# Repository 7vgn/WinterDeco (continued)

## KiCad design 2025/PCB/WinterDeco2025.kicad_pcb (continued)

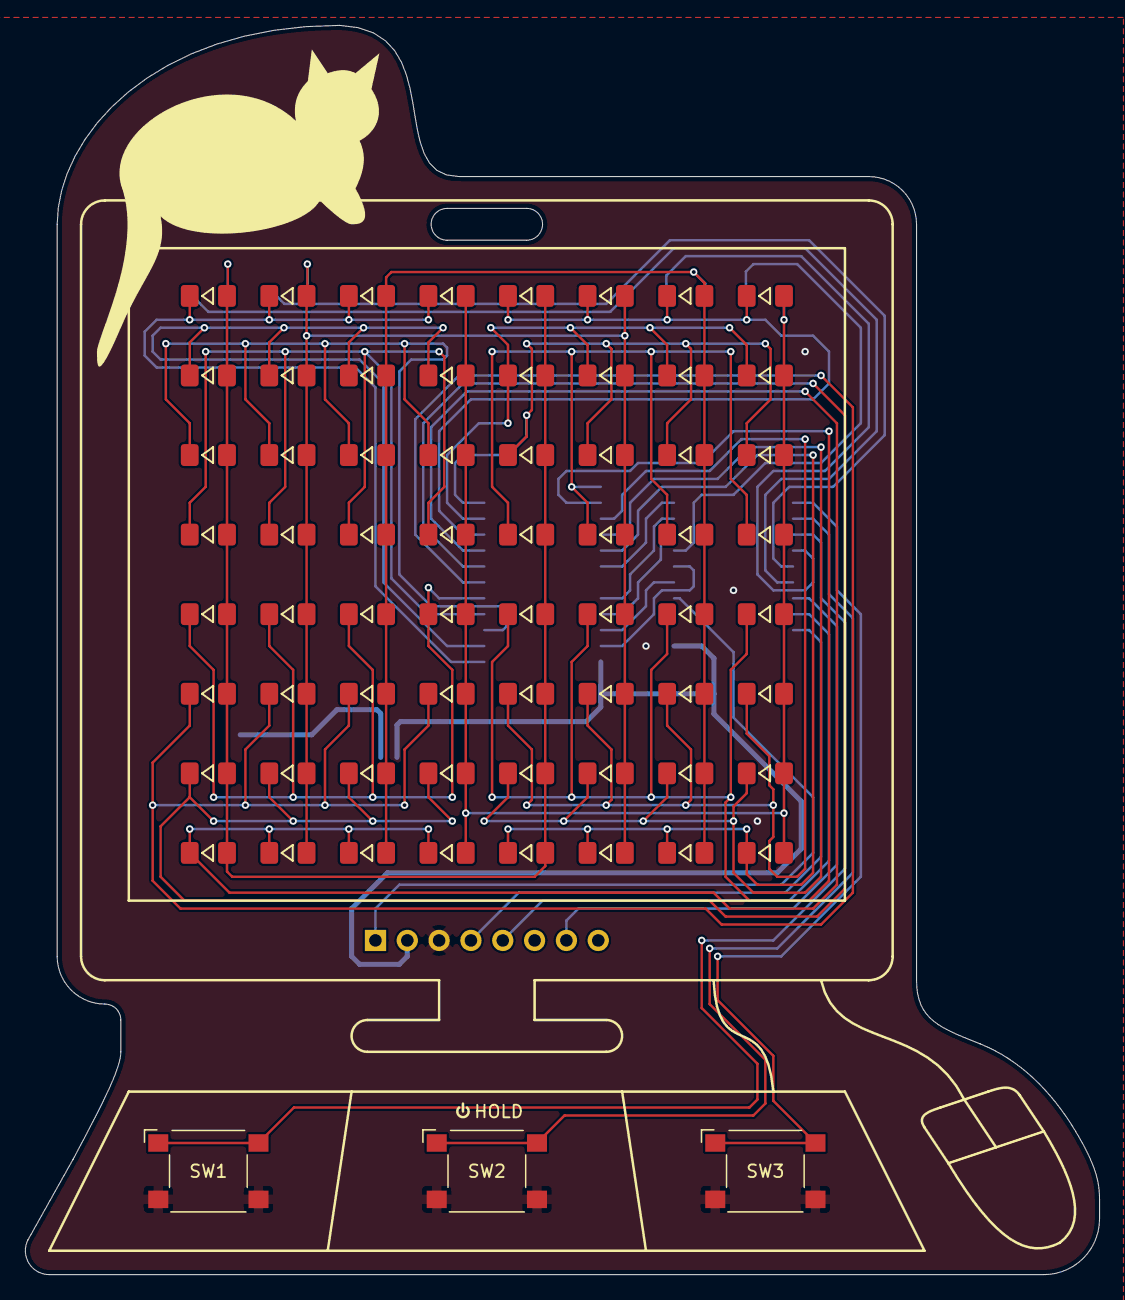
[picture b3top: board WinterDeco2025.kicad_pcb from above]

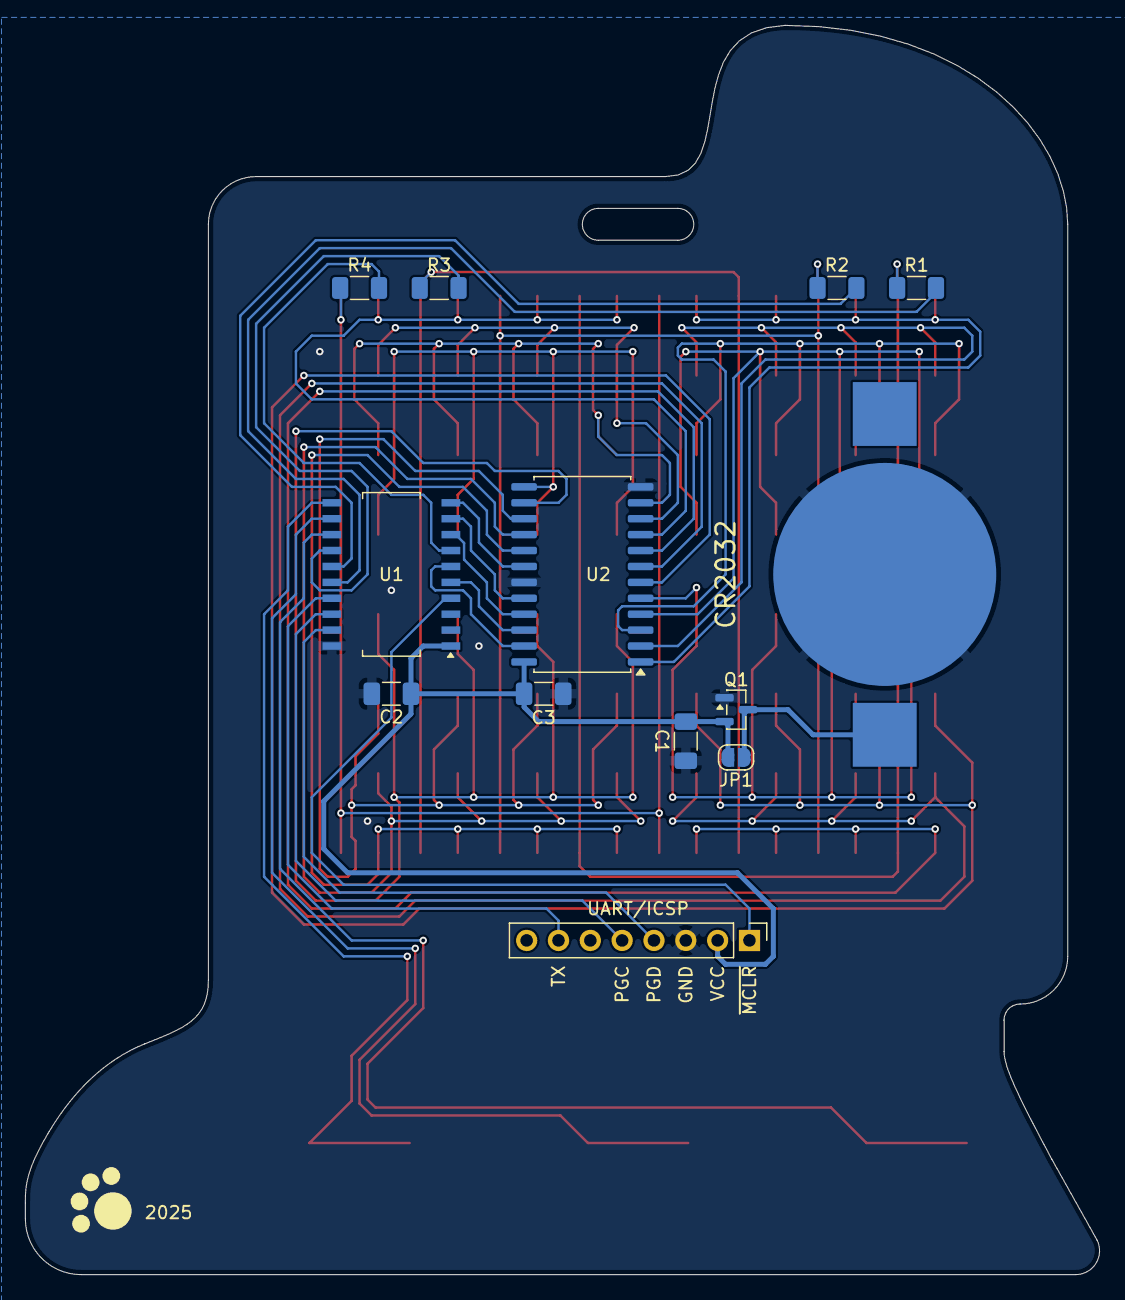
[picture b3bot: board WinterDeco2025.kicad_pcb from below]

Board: 2 copper layers, 85.7 x 99.7 mm, 80 parts (13 on the bottom side), 39 nets.

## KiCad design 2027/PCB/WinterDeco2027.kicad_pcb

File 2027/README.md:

> [!NOTE]
> This is a work in progress.

# Winter Decoration 2027

The 2027 winter-themed decoration is a spider web. This one has no buttons or touch sensors at all, using an accelerometer instead. 
As always, there is a hidden game. Can you find it without looking at the code?

## Bill of Materials

| Ref | Qty | Part | Value | Links[^links]
| --- | ---:| --- | --- | --- |
| - | 1 | PCB | 2-layer, 1.6mm thickness, purple soldermask, lead-free HASL | [J](https://jlcpcb.com/)
| BT1 | 1 | Battery Clip | CR2032, SMD mount | [M](https://mouser.com/ProductDetail/?qs=sGAEpiMZZMvxqoKe%252BDjhrhkd9JgmX6KPIe2Fc6FHFcOAlHTLYwGDJA%3D%3D) [D](https://www.digikey.com/en/products/detail/te-connectivity-linx/BAT-HLD-003-SMT-TR/14301788?s=N4IgTCBcDaIEIEEAqBaAEgGQCIoAy4GYUBlAWVSQCUQBdAXyA) [R](https://www.reichelt.de/shop/produkt/knopfzellenclip_fuer_20_mm_smd-56574)
| C1 | 1 | Capacitor | SMD 1206, 100µF, X5R | [M](https://mouser.com/ProductDetail/?qs=pUKx8fyJudDzdyEEakAKPA%3D%3D) [D](https://www.digikey.com/en/products/detail/murata-electronics/GRM31CR60J107KEA8L/16286000?s=N4IgTCBcDaIOICUCyBmAjAYQQNgAwCk1cB2AaQFEBBADgBkQBdAXyA) [R](https://www.reichelt.de/shop/produkt/mlcc_1206_100_f_6_3_v_-10_x5r-409219)
| C2..3 | 2 | Capacitor | SMD 1206, 100nF, X7R | [M](https://mouser.com/ProductDetail/?qs=Jm2GQyTW%2Fbgjukwx9JJFzw%3D%3D) [D](https://www.digikey.com/en/products/detail/kyocera-avx/KGM31DR72A104KU/563639?s=N4IgTCBcDaIIxgAwDY4GE6ICwGkCCAKmHiALoC%2BQA) [R](https://www.reichelt.de/shop/produkt/mlcc_1206_100_nf_100_v_-10_x7r-409241)
| C4 | 1 | Capacitor | SMD 1206, 1µF, tantalum | [M](https://mouser.com/ProductDetail/?qs=rZB7yXOqaoskTND3m0TpXQ%3D%3D) [D](https://www.digikey.com/en/products/detail/kemet/T491A105K016AT/818539) [R](https://www.reichelt.de/shop/produkt/smd-tantal_1_f_16v_125_c-393782)
| D1 | 1 | Photodiode | Infrared (850nm), 3mm | [M](https://mouser.com/ProductDetail/?qs=mAH9sUMRCttalcwxTBHy7g%3D%3D) [D](https://www.digikey.com/en/products/detail/inolux/INL-3ANPD80/10384782?s=N4IgTCBcDaIJIDkAyBaAzAQQQBQCIA4AGEAXQF8g) [A](https://aliexpress.com/item/1005007219440978.html)
| D* | 31 | LED | SMD 1206, yellow | [M](https://mouser.com/ProductDetail/?qs=sGAEpiMZZMv0DJfhVcWlK%252BdbpgZMtcHOeXAaxJ3bARo%3D) [D](https://www.digikey.com/en/products/detail/liteon/LTST-C150YKT/269217?s=N4IgTCBcDaIDIBUDKCC0BhAjAVgAwE0BpBEAXQF8g) [R](https://www.reichelt.de/shop/produkt/led_smd_1206_gelb_150_mcd_120_-361548)
| D* | 1 | LED | SMD 1206, red (back side) | [M](https://mouser.com/ProductDetail/?qs=sGAEpiMZZMv0DJfhVcWlK%252BdbpgZMtcHOPtGkXd2H%2F2o%3D) [D](https://www.digikey.com/en/products/detail/liteon/LTST-C150KRKT/386761?s=N4IgTCBcDaIDIBUDKCC0BhAjAVgAwGkAlfBEAXQF8g) [R](https://www.reichelt.de/de/de/shop/produkt/led_smd_1206_rot_150_mcd_120_-361547)
| Q1[^polprot] | 1 | P-MOSFET | IRLML6402, SOT-23 | [M](https://mouser.com/ProductDetail/?qs=9%252BKlkBgLFf0HuZuONx2Ewg%3D%3D) [D](https://www.digikey.com/en/products/detail/infineon-technologies/IRLML6402TRPBF/811437) [R](https://www.reichelt.de/shop/produkt/mosfet_p-ch_-20v_-3_7a_0_065r_sot-23-108743)
| R1..4 | 4 | Resistor | SMD 1206, 68Ω | [M](https://mouser.com/ProductDetail/?qs=CteSnpDdeuDJTICysoGhNw%3D%3D) [D](https://www.digikey.com/en/products/detail/yageo/RC1206JR-0768RL/729330?s=N4IgTCBcDaIEoGECMYAMA2AUnAtKg7OgBxwAyIAugL5A) [R](https://www.reichelt.de/shop/produkt/smd-widerstand_1206_68_ohm_250_mw_5_-18364)
| R5..6 | 2 | Resistor | SMD 1206, 4.7kΩ | [M](https://mouser.com/ProductDetail/?qs=CteSnpDdeuDgOu3Rsm1uRA%3D%3D) [D](https://www.digikey.com/en/products/detail/yageo/RC1206JR-074K7L/729295?s=N4IgTCBcDaIEoGECMYAMA2AUnAtKg7ACwDS%2BAMiALoC%2BQA) [R](https://www.reichelt.de/shop/produkt/smd-widerstand_1206_4_7_kohm_250_mw_5_-18330)
| U1 | 1 | Microcontroller | PIC18F14Q41-I/REB, VQFN-20 | [M](https://mouser.com/ProductDetail/?qs=W%2FMpXkg%252BdQ7pNqp6ZZCcjA%3D%3D) [D](https://www.digikey.com/en/products/detail/microchip-technology/PIC18F14Q41-I-REB/13622176?s=N4IgTCBcDaIAoEkDCBGAHAMRQFgIrZQFoEB6AJQFEAhEAXQF8g) [R](https://www.reichelt.de/shop/produkt/8-bit-picmicro_mikrocontroller_16_kb_64_mhz_vqfn-20-311094)
| U2 | 1 | Accelerometer | ADXL345, LGA-14 | [M](https://mouser.com/ProductDetail/?qs=WIvQP4zGanhoa7YOkGtvEg%3D%3D) [D](https://www.digikey.com/en/products/detail/analog-devices-inc/ADXL345BCCZ/2034829) [A](https://aliexpress.com/item/1005008097141961.html)
| - | 1 | Piece of String | |
| - | 1 | Coin Cell | CR2032 |

[^links]: Links are just examples. Other sellers are available and similar parts can be substituted.  
[^polprot]: Q1 protects against reverse polarity and is optional. If left out, the solder jumper JP1 must be bridged instead. 

Required tools and materials: soldering iron, lead-free solder, hot air station, solder paste, tweezers, flux, isopropyl alcohol for cleaning, PIC programmer

Soldering is significantly harder than last year, since the microcontroller and the accelerometer are QFN (Quad FLat No Leads) components. If you don't have or are unfamiliar with hot-air soldering equipment, you can try using a hotplate and low-temperature solder paste (Sn42Bi58) instead.

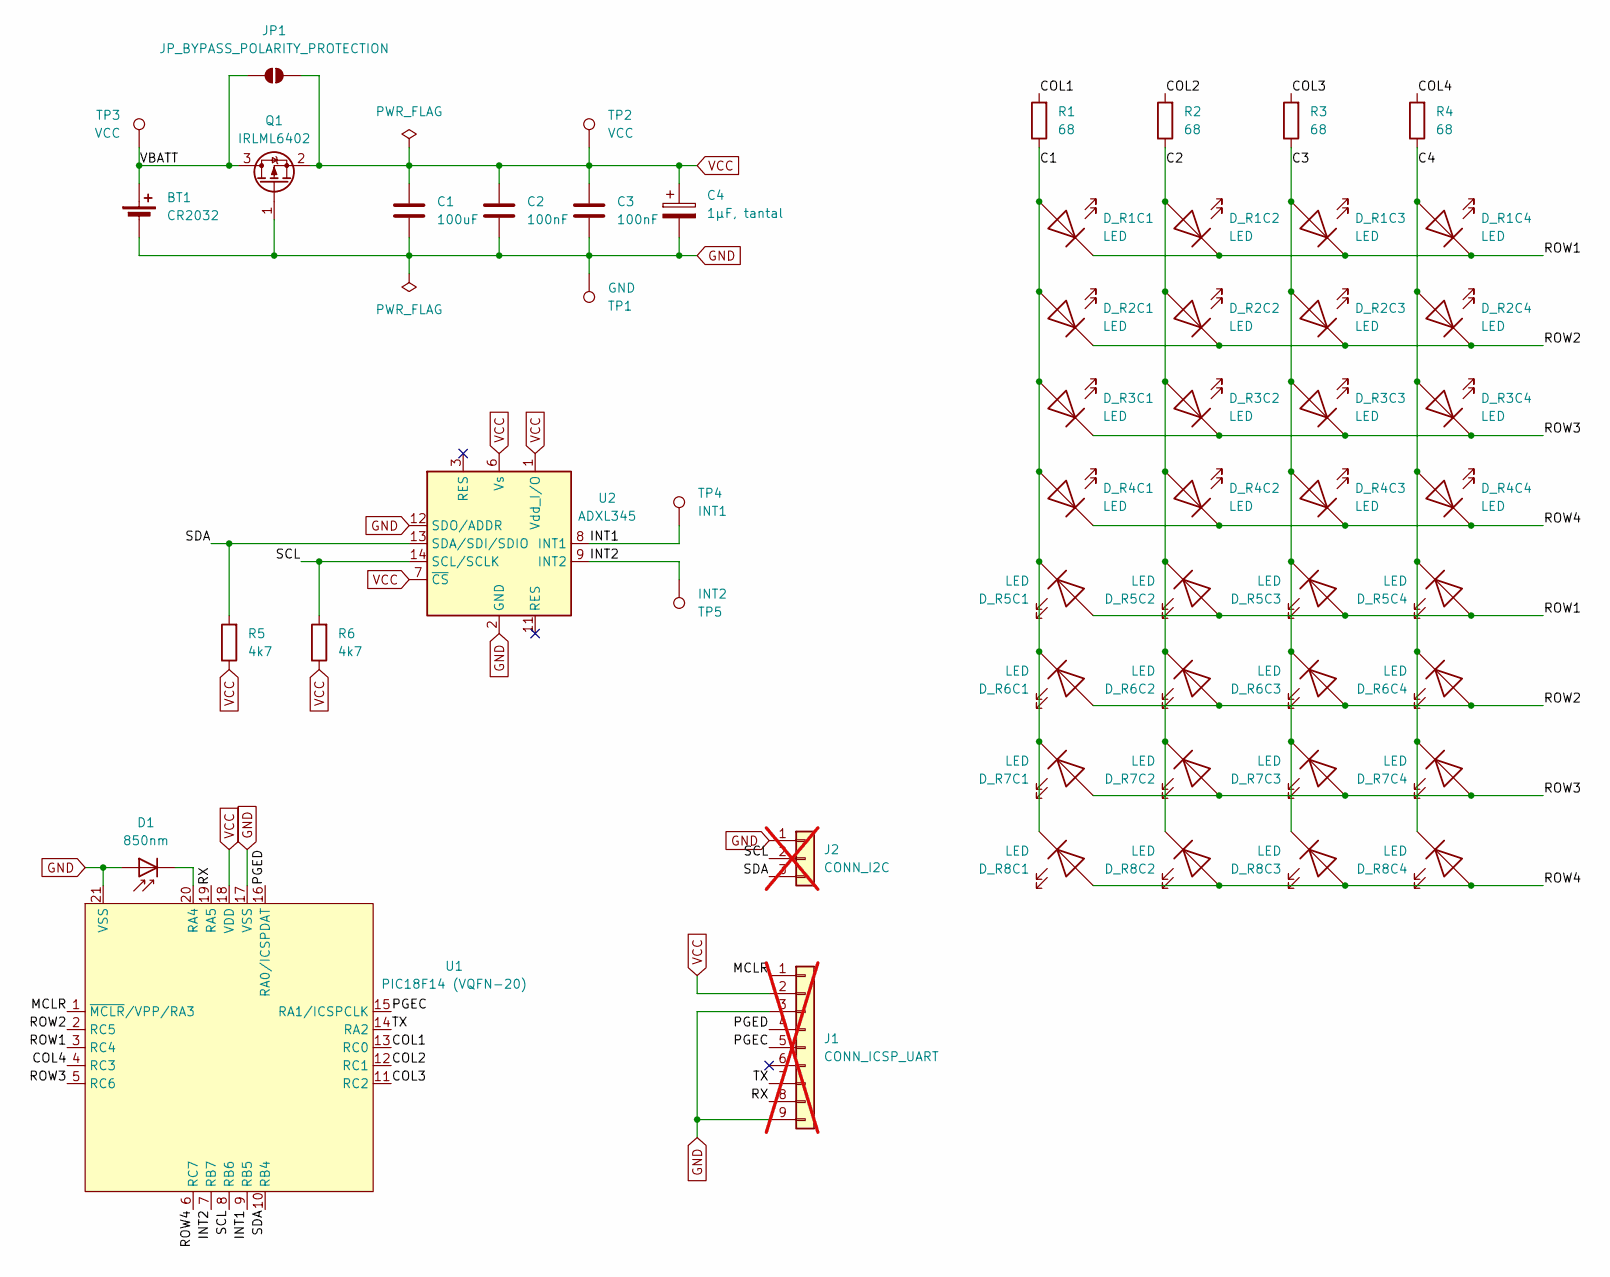
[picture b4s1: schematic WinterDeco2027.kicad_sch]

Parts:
BT1: CR2032; BatteryHolder_Keystone_3002_1x2032
C1: 100uF; C_1206_3216Metric_Pad1.33x1.80mm_HandSolder
C2, C3: 100nF; C_1206_3216Metric_Pad1.33x1.80mm_HandSolder
C4: 1µF, tantal; CP_EIA-3216-18_Kemet-A_HandSolder
D1: 850nm; LED_D3.0mm
D_R1C1, D_R1C2, D_R1C3, D_R1C4, D_R2C1, D_R2C2, D_R2C3, D_R2C4, D_R3C1, D_R3C2, D_R3C3, D_R3C4, D_R4C1, D_R4C2, D_R4C3, D_R4C4, D_R5C1, D_R5C2, D_R5C3, D_R5C4, D_R6C1, D_R6C2, D_R6C3, D_R6C4, D_R7C1, D_R7C2, D_R7C3, D_R7C4, D_R8C1, D_R8C2, D_R8C3, D_R8C4: LED; LED_1206_3216Metric_Pad1.42x1.75mm_Arrow_HandSolder
J1: CONN_ICSP_UART; PinHeader_1x09_P2.54mm_Vertical; not fitted
J2: CONN_I2C; JST_SH_BM03B-SRSS-TB_1x03-1MP_P1.00mm_Vertical; not fitted
JP1: JP_BYPASS_POLARITY_PROTECTION; SolderJumper-2_P1.3mm_Open_RoundedPad1.0x1.5mm
Q1: IRLML6402; SOT-23_Handsoldering
R1, R2, R3, R4: 68; R_1206_3216Metric_Pad1.30x1.75mm_HandSolder
R5, R6: 4k7; R_1206_3216Metric_Pad1.30x1.75mm_HandSolder
TP1: GND; TestPoint_Pad_D1.5mm
TP2, TP3: VCC; TestPoint_Pad_D1.5mm
TP4: INT1; TestPoint_Pad_D1.5mm
TP5: INT2; TestPoint_Pad_D1.5mm
U1: PIC18F14 (VQFN-20); VQFN-20-1EP_3x3mm_P0.4mm_EP1.7x1.7mm_ThermalVias
U2: ADXL345; LGA-14_3x5mm_P0.8mm_LayoutBorder1x6y

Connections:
/C1: D_R1C1.2 (A), D_R2C1.2 (A), D_R3C1.2 (A), D_R4C1.2 (A), D_R5C1.1 (K), D_R6C1.1 (K), D_R7C1.1 (K), D_R8C1.1 (K), R1.1
/C2: D_R1C2.2 (A), D_R2C2.2 (A), D_R3C2.2 (A), D_R4C2.2 (A), D_R5C2.1 (K), D_R6C2.1 (K), D_R7C2.1 (K), D_R8C2.1 (K), R2.1
/C3: D_R1C3.2 (A), D_R2C3.2 (A), D_R3C3.2 (A), D_R4C3.2 (A), D_R5C3.1 (K), D_R6C3.1 (K), D_R7C3.1 (K), D_R8C3.1 (K), R3.1
/C4: D_R1C4.2 (A), D_R2C4.2 (A), D_R3C4.2 (A), D_R4C4.2 (A), D_R5C4.1 (K), D_R6C4.1 (K), D_R7C4.1 (K), D_R8C4.1 (K), R4.1
/COL1: R1.2, U1.13 (RC0)
/COL2: R2.2, U1.12 (RC1)
/COL3: R3.2, U1.11 (RC2)
/COL4: R4.2, U1.4 (RC3)
/INT1: TP4.1 (1_1), U1.9 (RB5), U2.8 (INT1)
/INT2: TP5.1 (1_1), U1.7 (RB7), U2.9 (INT2)
/MCLR: J1.1, U1.1 (~MCLR/VPP/RA3)
/PGEC: J1.5, U1.15 (RA1/ICSPCLK)
/PGED: J1.4, U1.16 (RA0/ICSPDAT)
/ROW1: D_R1C1.1 (K), D_R1C2.1 (K), D_R1C3.1 (K), D_R1C4.1 (K), D_R5C1.2 (A), D_R5C2.2 (A), D_R5C3.2 (A), D_R5C4.2 (A), U1.3 (RC4)
/ROW2: D_R2C1.1 (K), D_R2C2.1 (K), D_R2C3.1 (K), D_R2C4.1 (K), D_R6C1.2 (A), D_R6C2.2 (A), D_R6C3.2 (A), D_R6C4.2 (A), U1.2 (RC5)
/ROW3: D_R3C1.1 (K), D_R3C2.1 (K), D_R3C3.1 (K), D_R3C4.1 (K), D_R7C1.2 (A), D_R7C2.2 (A), D_R7C3.2 (A), D_R7C4.2 (A), U1.5 (RC6)
/ROW4: D_R4C1.1 (K), D_R4C2.1 (K), D_R4C3.1 (K), D_R4C4.1 (K), D_R8C1.2 (A), D_R8C2.2 (A), D_R8C3.2 (A), D_R8C4.2 (A), U1.6 (RC7)
/RX: J1.8, U1.19 (RA5)
/SCL: J2.2, R6.2, U1.8 (RB6), U2.14 (SCL/SCLK)
/SDA: J2.3, R5.2, U1.10 (RB4), U2.13 (SDA/SDI/SDIO)
/TX: J1.7, U1.14 (RA2)
/VBATT: BT1.1 (+), JP1.1 (A), Q1.3 (D), TP3.1 (1_1)
GND: BT1.2 (-), C1.2, C2.2, C3.2, C4.2, D1.2 (A), J1.3, J1.9, J2.1, Q1.1 (G), TP1.1 (1_1), U1.17 (VSS), U1.21 (VSS), U2.2 (GND), U2.4 (GND), U2.5 (GND), U2.12 (SDO/ADDR)
unnamed: D1.1 (K), U1.20 (RA4)
VCC: C1.1, C2.1, C3.1, C4.1, J1.2, JP1.2 (B), Q1.2 (S), R5.1, R6.1, TP2.1 (1_1), U1.18 (VDD), U2.1 (Vdd_I/O), U2.6 (Vs), U2.7 (~CS)

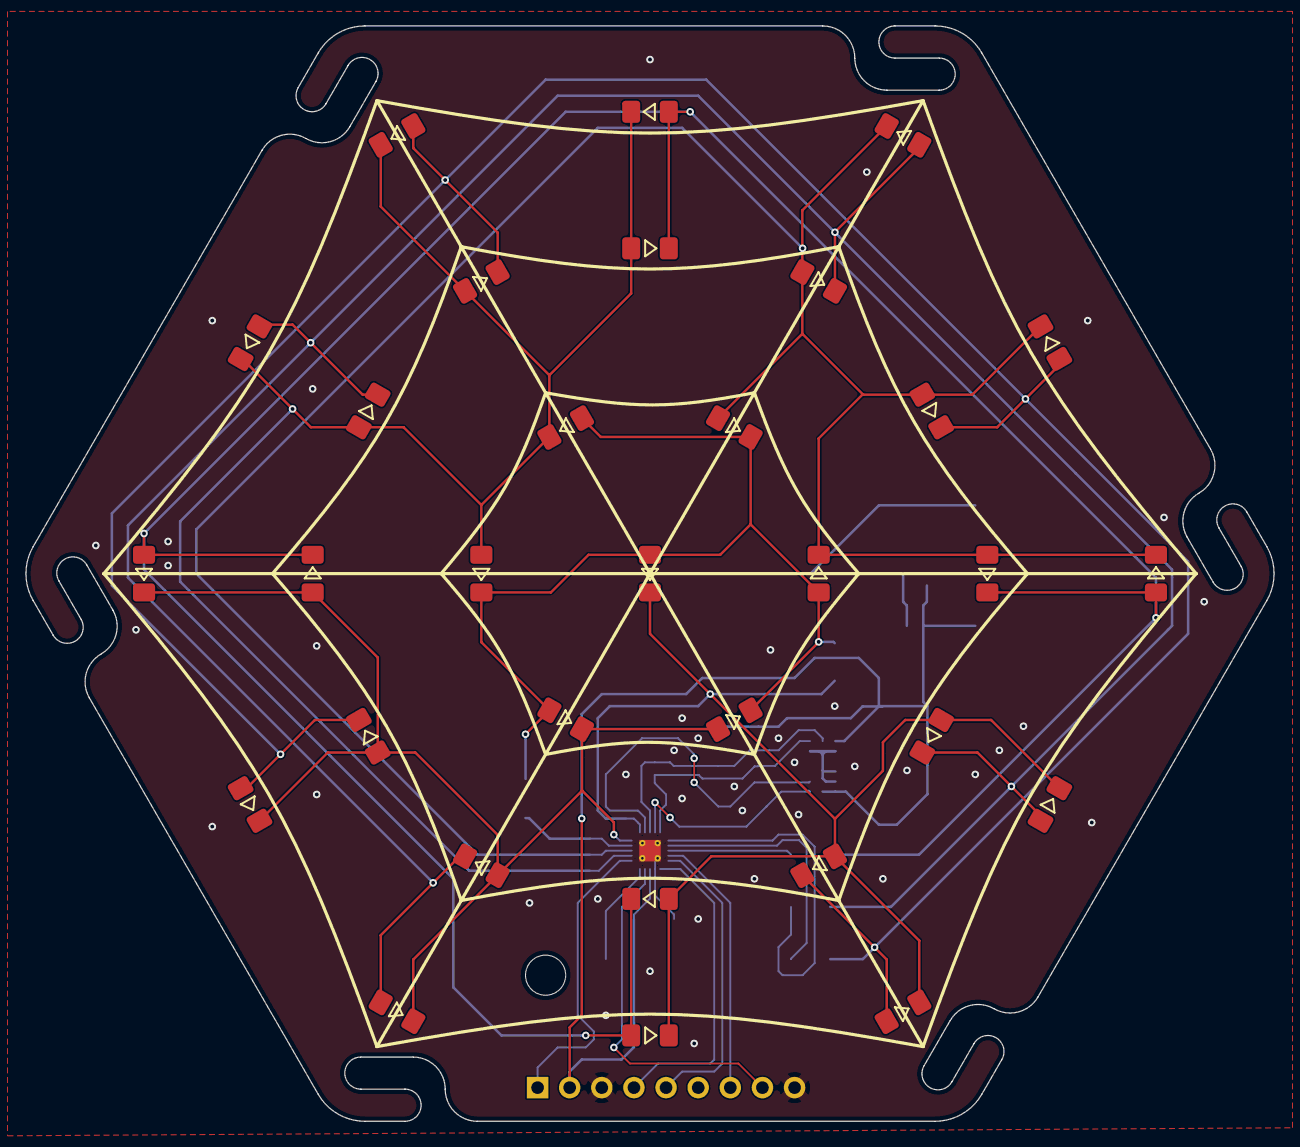
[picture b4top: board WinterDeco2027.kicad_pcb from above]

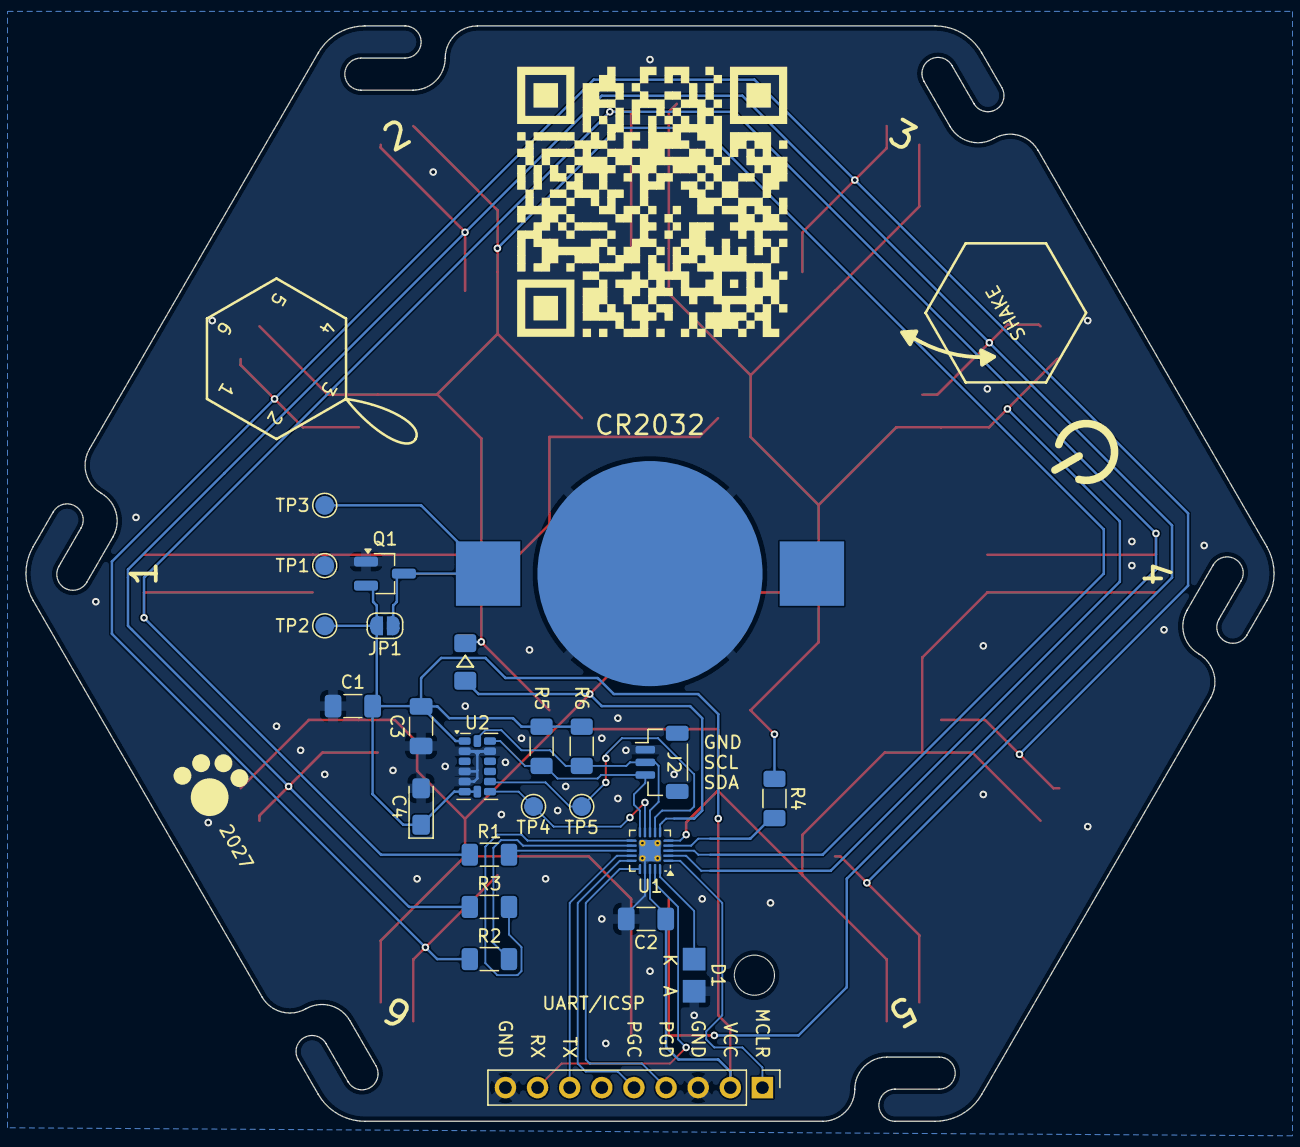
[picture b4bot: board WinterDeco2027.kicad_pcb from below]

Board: 2 copper layers, 98.7 x 86.6 mm, 55 parts (24 on the bottom side), 25 nets.

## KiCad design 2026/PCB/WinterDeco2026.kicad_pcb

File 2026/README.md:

# Winter Decoration 2026

The 2026 winter-themed decoration is a star. The touch sensors are back this year and bi-color LEDs have their debut. 
As always, there is a hidden game. Can you find it without looking at the code?

## Bill of Materials

| Ref | Qty | Part | Value | Links[^links]
| --- | ---:| --- | --- | --- |
| - | 1 | PCB | 2-layer, 1.6mm thickness, yellow soldermask, lead-free HASL | [J](https://jlcpcb.com/)
| BT1 | 1 | Battery Clip | CR2032, SMD mount | [M](https://mouser.com/ProductDetail/?qs=sGAEpiMZZMvxqoKe%252BDjhrhkd9JgmX6KPIe2Fc6FHFcOAlHTLYwGDJA%3D%3D) [D](https://www.digikey.com/en/products/detail/te-connectivity-linx/BAT-HLD-003-SMT-TR/14301788?s=N4IgTCBcDaIEIEEAqBaAEgGQCIoAy4GYUBlAWVSQCUQBdAXyA) [R](https://www.reichelt.de/shop/produkt/knopfzellenclip_fuer_20_mm_smd-56574)
| C1 | 1 | Capacitor | SMD 1206, 100µF, X5R | [M](https://mouser.com/ProductDetail/?qs=pUKx8fyJudDzdyEEakAKPA%3D%3D) [D](https://www.digikey.com/en/products/detail/murata-electronics/GRM31CR60J107KEA8L/16286000?s=N4IgTCBcDaIOICUCyBmAjAYQQNgAwCk1cB2AaQFEBBADgBkQBdAXyA) [R](https://www.reichelt.de/shop/produkt/mlcc_1206_100_f_6_3_v_-10_x5r-409219)
| C2 | 1 | Capacitor | SMD 1206, 100nF, X7R | [M](https://mouser.com/ProductDetail/?qs=Jm2GQyTW%2Fbgjukwx9JJFzw%3D%3D) [D](https://www.digikey.com/en/products/detail/kyocera-avx/KGM31DR72A104KU/563639?s=N4IgTCBcDaIIxgAwDY4GE6ICwGkCCAKmHiALoC%2BQA) [R](https://www.reichelt.de/shop/produkt/mlcc_1206_100_nf_100_v_-10_x7r-409241)
| D1..9 | 9 | LED | SMD 1210 (3227), red/green bi-color | [M](https://mouser.com/ProductDetail/?qs=%252BpvKPZD0HfH4fMARFecNqA%3D%3D) [D](https://www.digikey.com/en/products/detail/kingbright/APB3227SURKCGKC/4098592?s=N4IgTCBcDaIDYFMAmACAzGMB2EBdAvkA) [A](https://www.aliexpress.com/item/1005003327335162.html)
| D10..21 | 12 | LED | SMD 1206 (3216), yellow | [M](https://mouser.com/ProductDetail/?qs=sGAEpiMZZMv0DJfhVcWlK%252BdbpgZMtcHOeXAaxJ3bARo%3D) [D](https://www.digikey.com/en/products/detail/liteon/LTST-C150YKT/269217?s=N4IgTCBcDaIDIBUDKCC0BhAjAVgAwE0BpBEAXQF8g) [R](https://www.reichelt.de/shop/produkt/led_smd_1206_gelb_150_mcd_120_-361548)
| Q1[^polprot] | 1 | P-MOSFET | IRLML6402, SOT-23 | [M](https://mouser.com/ProductDetail/?qs=9%252BKlkBgLFf0HuZuONx2Ewg%3D%3D) [D](https://www.digikey.com/en/products/detail/infineon-technologies/IRLML6402TRPBF/811437) [R](https://www.reichelt.de/shop/produkt/mosfet_p-ch_-20v_-3_7a_0_065r_sot-23-108743)
| R1..3 | 3 | Resistor | SMD 1206, 68Ω | [M](https://mouser.com/ProductDetail/?qs=CteSnpDdeuDJTICysoGhNw%3D%3D) [D](https://www.digikey.com/en/products/detail/yageo/RC1206JR-0768RL/729330?s=N4IgTCBcDaIEoGECMYAMA2AUnAtKg7OgBxwAyIAugL5A) [R](https://www.reichelt.de/shop/produkt/smd-widerstand_1206_68_ohm_250_mw_5_-18364)
| R4 | 1 | Resistor | SMD 1206, 3.3kΩ | [M](https://mouser.com/ProductDetail/?qs=CteSnpDdeuDJAlQtfVL%252BIw%3D%3D) [D](https://www.digikey.com/en/products/detail/yageo/RC1206JR-073K3L/729267?s=N4IgTCBcDaIEoGECMYAMA2AUnAtKg7AMwDShAMiALoC%2BQA) [R](https://www.reichelt.de/shop/produkt/smd-widerstand_1206_3_3_kohm_250_mw_5_-18302)
| R5 | 1 | Resistor | SMD 1206, 4.7kΩ | [M](https://mouser.com/ProductDetail/?qs=CteSnpDdeuDgOu3Rsm1uRA%3D%3D) [D](https://www.digikey.com/en/products/detail/yageo/RC1206JR-074K7L/729295?s=N4IgTCBcDaIEoGECMYAMA2AUnAtKg7ACwDS%2BAMiALoC%2BQA) [R](https://www.reichelt.de/shop/produkt/smd-widerstand_1206_4_7_kohm_250_mw_5_-18330)
| U1 | 1 | Microcontroller | PIC18F14Q41-I/SS, TSSOP-20 | [M](https://www.mouser.com/ProductDetail/?qs=W%2FMpXkg%252BdQ7EgyN%2FoU%2FgZA%3D%3D) [D](https://www.digikey.com/en/products/detail/microchip-technology/PIC18F14Q41-I-SS/13534584?s=N4IgTCBcDaIAoEkDCBGAHAMRQFgIrZQFoEB6AZzJAF0BfIA) [R](https://www.reichelt.de/de/de/shop/produkt/8-bit-picmicro_mikrocontroller_16_kb_64_mhz_ssop-20-311093)
| - | 1 | Piece of String | |
| - | 1 | Coin Cell | CR2032 |

[^links]: Links are just examples. Other sellers are available and similar parts can be substituted.  
[^polprot]: Q1 protects against reverse polarity and is optional. If left out, the solder jumper JP1 must be bridged instead. 

Required tools and materials: soldering iron, lead-free solder, tweezers, flux, isopropyl alcohol for cleaning, PIC programmer

Soldering is slightly more challenging than in previous years, since the microcontroller is SSOP instead of SOIC.

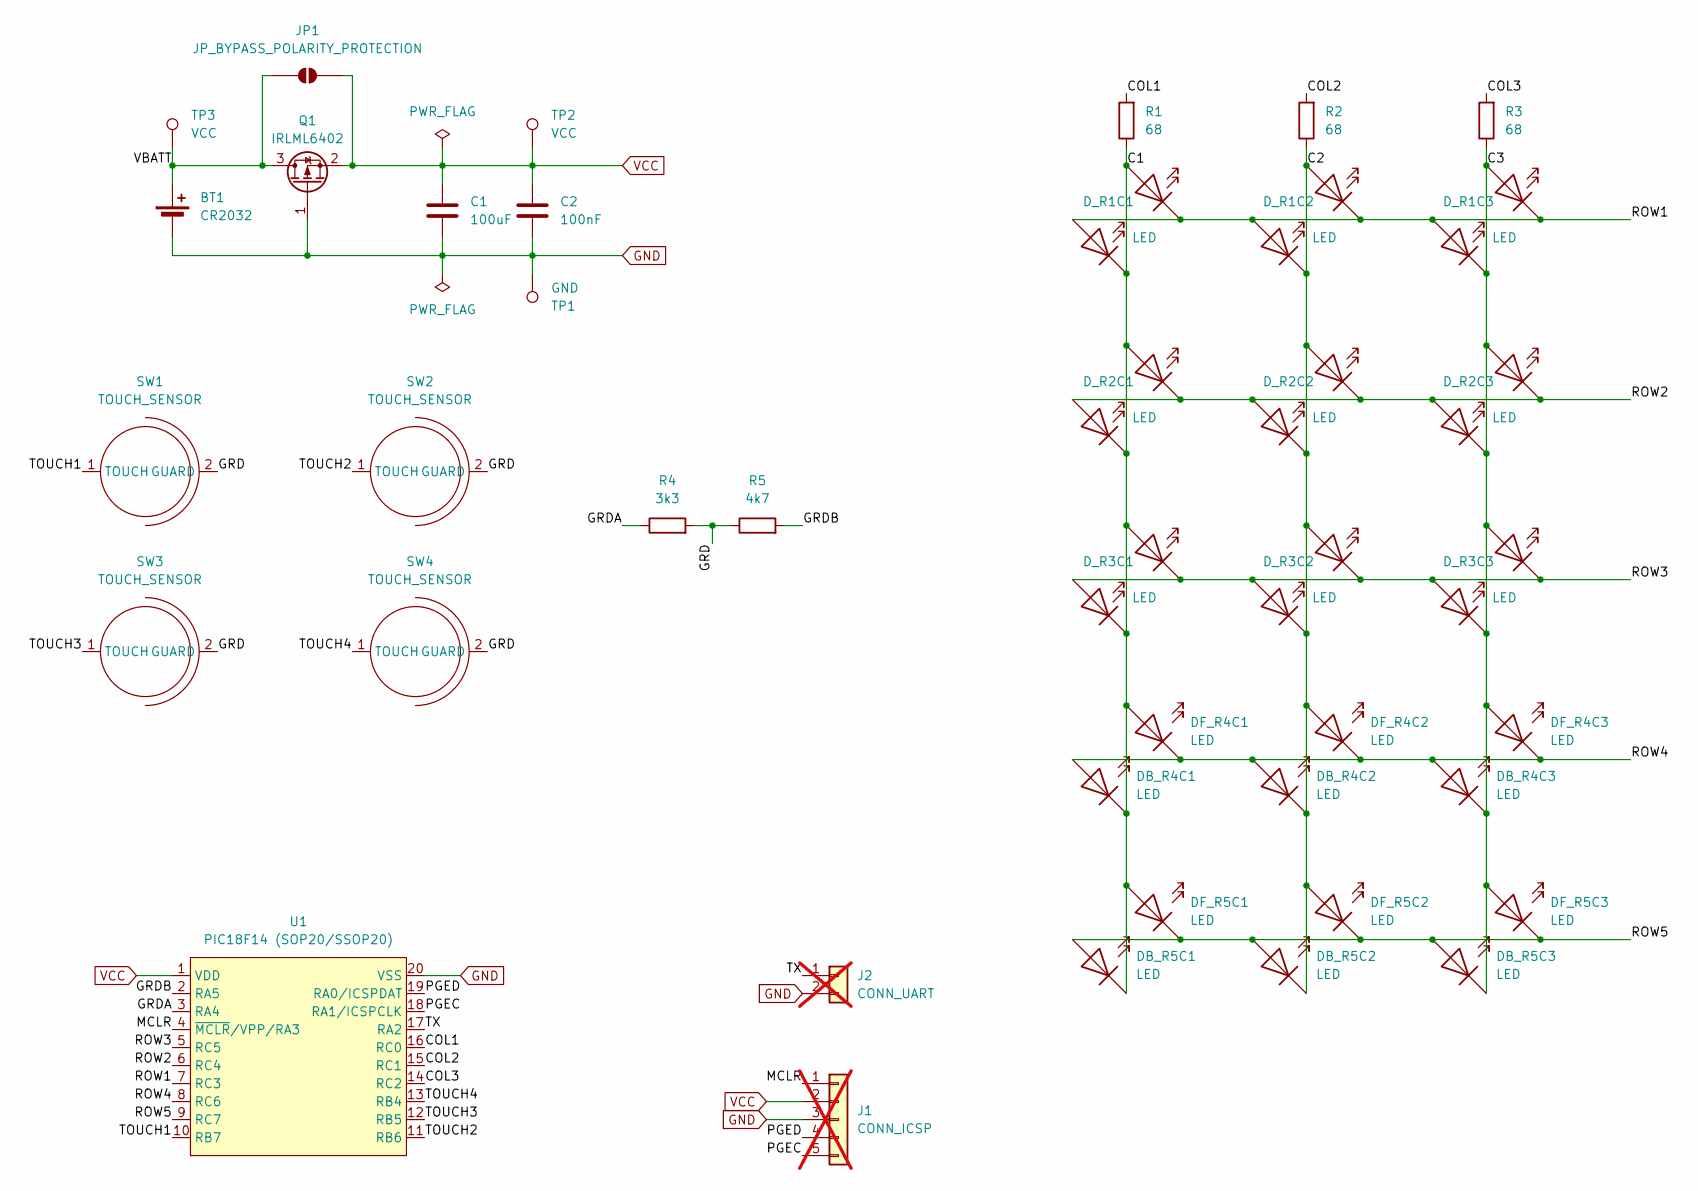
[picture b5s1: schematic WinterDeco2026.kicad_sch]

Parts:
BT1: CR2032; BatteryHolder_Keystone_3002_1x2032
C1: 100uF; C_1206_3216Metric_Pad1.33x1.80mm_HandSolder
C2: 100nF; C_1206_3216Metric_Pad1.33x1.80mm_HandSolder
DB_R4C1, DB_R4C2, DB_R4C3, DB_R5C1, DB_R5C2, DB_R5C3: LED; LED_1206_3216Metric_Pad1.42x1.75mm_Arrow_HandSolder
DF_R4C1, DF_R4C2, DF_R4C3, DF_R5C1, DF_R5C2, DF_R5C3: LED; LED_1206_3216Metric_Pad1.42x1.75mm_Arrow_HandSolder
D_R1C1, D_R1C2, D_R1C3, D_R2C1, D_R2C2, D_R2C3, D_R3C1, D_R3C2, D_R3C3: LED; LED_1210_3227_Bicolor
J1: CONN_ICSP; PinHeader_1x05_P2.54mm_Vertical; not fitted
J2: CONN_UART; PinHeader_1x02_P2.54mm_Vertical; not fitted
JP1: JP_BYPASS_POLARITY_PROTECTION; SolderJumper-2_P1.3mm_Open_RoundedPad1.0x1.5mm
Q1: IRLML6402; SOT-23_Handsoldering
R1, R2, R3: 68; R_1206_3216Metric_Pad1.30x1.75mm_HandSolder
R4: 3k3; R_1206_3216Metric_Pad1.30x1.75mm_HandSolder
R5: 4k7; R_1206_3216Metric_Pad1.30x1.75mm_HandSolder
SW1, SW2, SW3, SW4: TOUCH_SENSOR; Touch Sensor
TP1: GND; TestPoint_Pad_D1.5mm
TP2, TP3: VCC; TestPoint_Pad_D1.5mm
U1: PIC18F14 (SOP20/SSOP20); TSSOP-20_4.4x6.5mm_P0.65mm

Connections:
/C1: DB_R4C1.1 (K), DB_R5C1.1 (K), DF_R4C1.2 (A), DF_R5C1.2 (A), D_R1C1.2 (K), D_R1C1.3 (A), D_R2C1.2 (K), D_R2C1.3 (A), D_R3C1.2 (K), D_R3C1.3 (A), R1.1
/C2: DB_R4C2.1 (K), DB_R5C2.1 (K), DF_R4C2.2 (A), DF_R5C2.2 (A), D_R1C2.2 (K), D_R1C2.3 (A), D_R2C2.2 (K), D_R2C2.3 (A), D_R3C2.2 (K), D_R3C2.3 (A), R2.1
/C3: DB_R4C3.1 (K), DB_R5C3.1 (K), DF_R4C3.2 (A), DF_R5C3.2 (A), D_R1C3.2 (K), D_R1C3.3 (A), D_R2C3.2 (K), D_R2C3.3 (A), D_R3C3.2 (K), D_R3C3.3 (A), R3.1
/COL1: R1.2, U1.16 (RC0)
/COL2: R2.2, U1.15 (RC1)
/COL3: R3.2, U1.14 (RC2)
/GRD: R4.2, R5.1, SW1.2 (GUARD), SW2.2 (GUARD), SW3.2 (GUARD), SW4.2 (GUARD)
/GRDA: R4.1, U1.3 (RA4)
/GRDB: R5.2, U1.2 (RA5)
/MCLR: J1.1, U1.4 (~MCLR/VPP/RA3)
/PGEC: J1.5, U1.18 (RA1/ICSPCLK)
/PGED: J1.4, U1.19 (RA0/ICSPDAT)
/ROW1: D_R1C1.1 (A), D_R1C1.4 (K), D_R1C2.1 (A), D_R1C2.4 (K), D_R1C3.1 (A), D_R1C3.4 (K), U1.7 (RC3)
/ROW2: D_R2C1.1 (A), D_R2C1.4 (K), D_R2C2.1 (A), D_R2C2.4 (K), D_R2C3.1 (A), D_R2C3.4 (K), U1.6 (RC4)
/ROW3: D_R3C1.1 (A), D_R3C1.4 (K), D_R3C2.1 (A), D_R3C2.4 (K), D_R3C3.1 (A), D_R3C3.4 (K), U1.5 (RC5)
/ROW4: DB_R4C1.2 (A), DB_R4C2.2 (A), DB_R4C3.2 (A), DF_R4C1.1 (K), DF_R4C2.1 (K), DF_R4C3.1 (K), U1.8 (RC6)
/ROW5: DB_R5C1.2 (A), DB_R5C2.2 (A), DB_R5C3.2 (A), DF_R5C1.1 (K), DF_R5C2.1 (K), DF_R5C3.1 (K), U1.9 (RC7)
/TOUCH1: SW1.1 (TOUCH), U1.10 (RB7)
/TOUCH2: SW2.1 (TOUCH), U1.11 (RB6)
/TOUCH3: SW3.1 (TOUCH), U1.12 (RB5)
/TOUCH4: SW4.1 (TOUCH), U1.13 (RB4)
/TX: J2.1, U1.17 (RA2)
/VBATT: BT1.1 (+), JP1.1 (A), Q1.3 (D), TP3.1 (1_1)
GND: BT1.2 (-), C1.2, C2.2, J1.3, J2.2, Q1.1 (G), TP1.1 (1_1), U1.20 (VSS)
VCC: C1.1, C2.1, J1.2, JP1.2 (B), Q1.2 (S), TP2.1 (1_1), U1.1 (VDD)

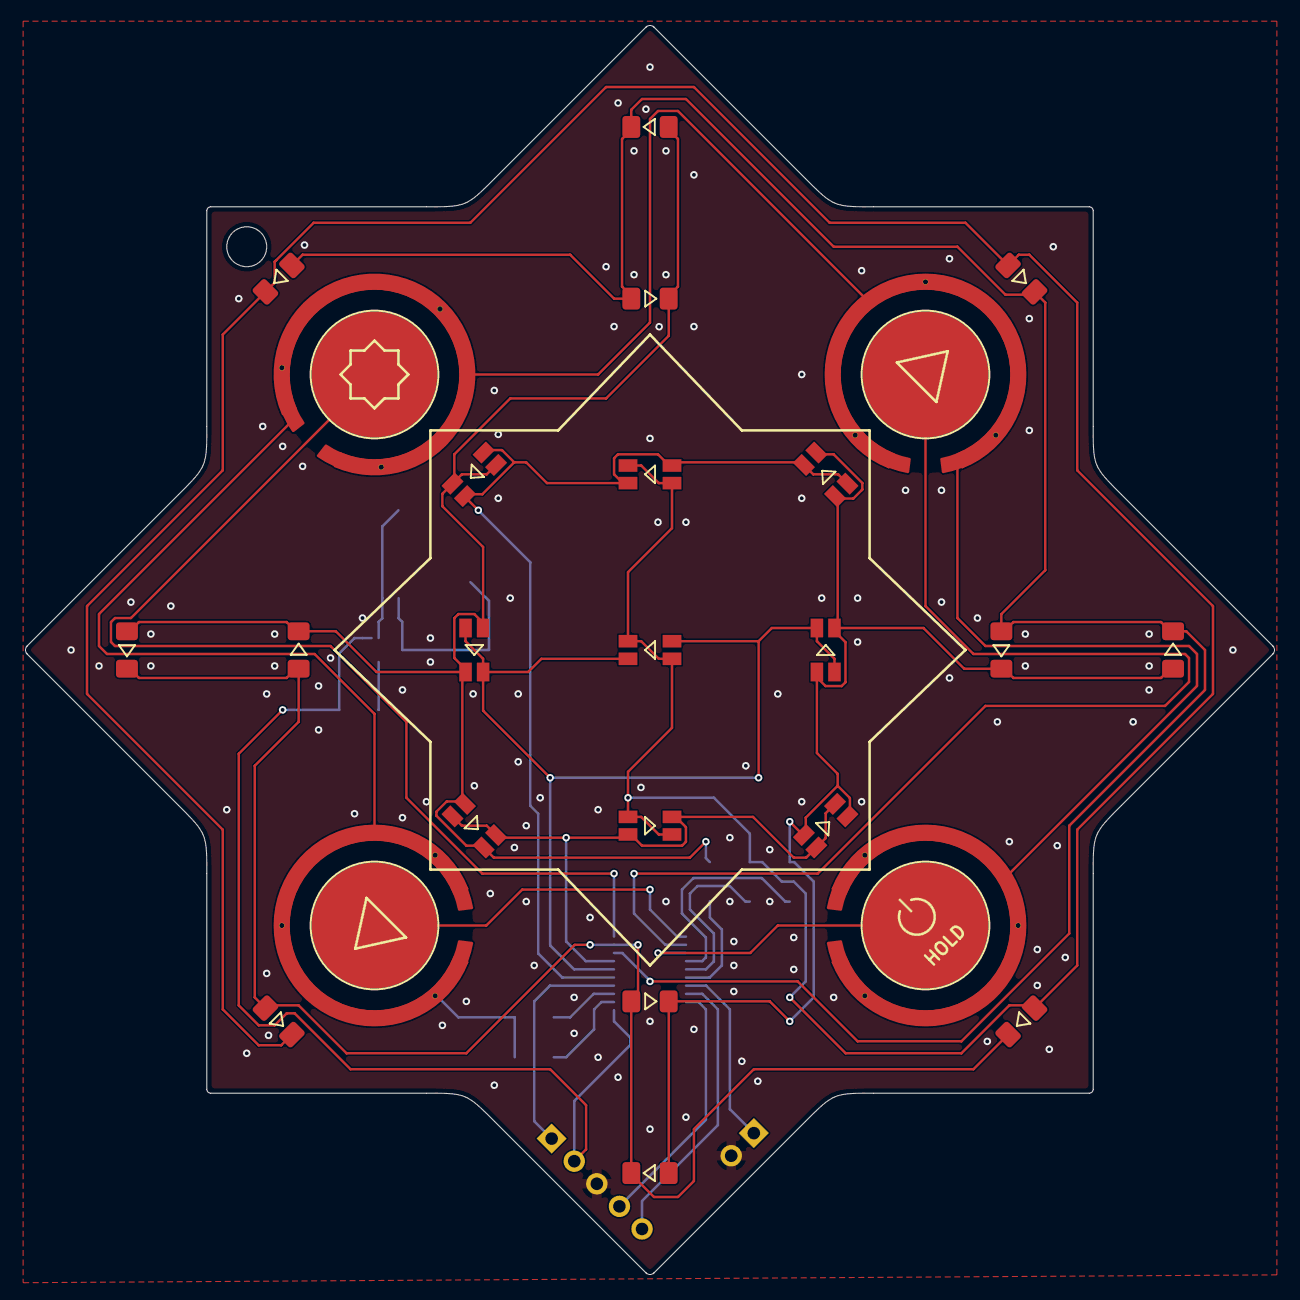
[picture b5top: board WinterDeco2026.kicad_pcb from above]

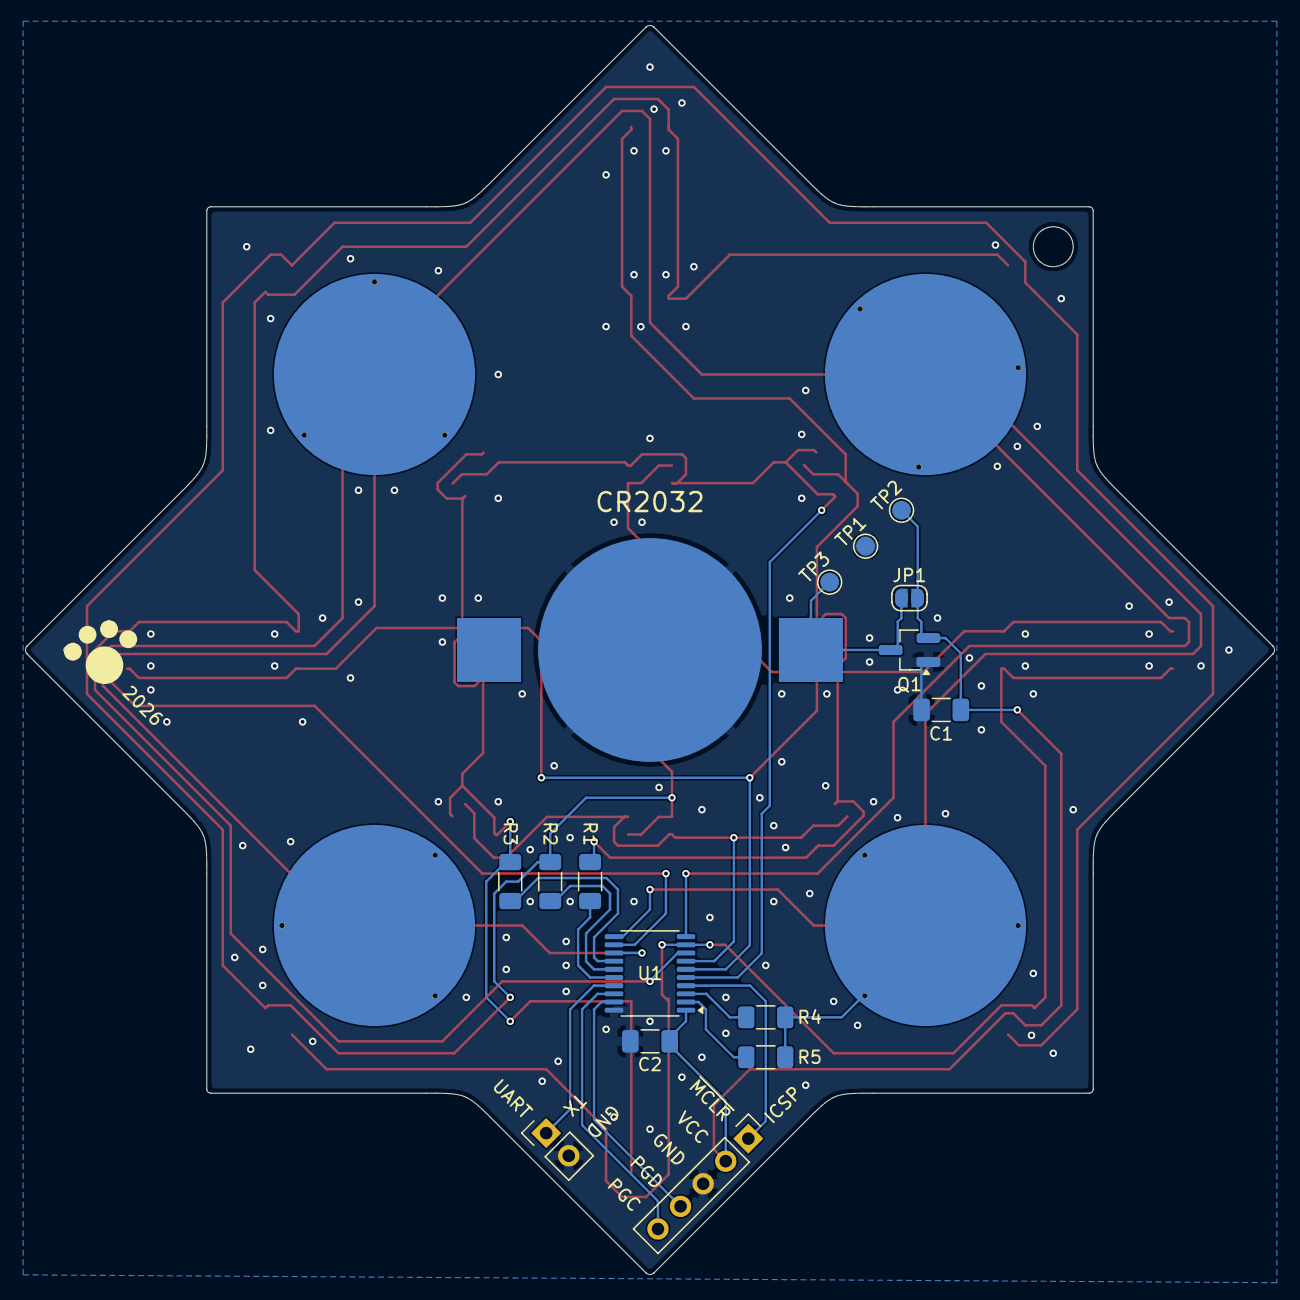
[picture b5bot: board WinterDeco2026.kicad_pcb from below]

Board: 2 copper layers, 99.3 x 99.3 mm, 41 parts (16 on the bottom side), 25 nets.

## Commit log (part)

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2025-09-26 Testing HTML file
2025-10-05 Testing markdown syntax
2025-10-05 Added 2023 PCB
2025-10-05 Fixed KiCAD ignores
2025-10-05 Fixed MPLAB X ignores
2025-10-06 Fixed swapped rows and columns
2025-10-06 Added PCBs
2025-10-06 Fixed table formatting
2025-10-06 Fixed microcontroller package and links
2025-10-25 Finished 2025 firmware
2025-10-25 Fixed overly broad ignore direcives
2025-10-25 Fixed typo
2025-10-27 Cosmetic corrections
2025-10-27 2023 Firmware
2025-10-27 Fixed compiler warnings
2025-10-27 Added 2024 Firmware
